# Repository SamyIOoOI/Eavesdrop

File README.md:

<h1 align="center">Eavesdrop</h1>

### <p align="center">[Main Features](#main-features) **-** [Usage](#usage-of-eavesdrop) **-** [PCB & Schematic](#design) **-** [Gerber Files](/Eavesdrop/Gerber%20Files/) **-** [Kicad (Schematic & PCB)](/Eavesdrop/Kicad%20Source%20Files/)  **-** [BOM](#bom)  **-** [BOM (File)](/BOM/evasdrop.xlsx) **-** [Credits](#credits)</p>

## How would you feel if your own fridge was spying on you? Maybe even your tv, maybe the fryer, maybe the wall outlet you charge this device with. maybe even your charger. Well that could very well be a carrier bug. Just like Eavesdrop.

*A "current carrier bug" is a spy tool that records the sound inside the area its plugged in and sends it back through the AC power its connected to directly, evading most detection devices available in the market that rely on RF to detect these devices.*

----------------

**<p align="center">No matter where you are. The bug listens as long as there's electricity flowing in the bugged device.<p>**

---------------

## Main Features

- Undetectable (via RF Detectors that are commonly used)
- Secretive (but requires prior access to the room)

- **Can be planted into any device, your lamp, your tv, your pc, ANYTHING can become a bug with one plug.**

## Usage of Eavesdrop

1- Insert it into the outlet or any device that takes in power from the wall and make sure the microphone jack is connected to proper microphone element such as an electret mic.

2- Connect the passive & active AC wires to their respective locations via the male header on the pcb, each header reads if its N (neutral) or L (live). 
Reversal could cause irreversible damage. Use a test screw driver to make sure you're connecting the right ones.

3- connect the receiver , when required to listen to the broadcast, to an outlet that is in the same grid as the target room/building.

4- Make sure that both the receiver and the sender are at the same wavelength via calibration. Refer to the schemati for more details.

5- Use the volume control knob to increase/decrease th sound level.

<br>

<p align="center">Note that usage of Eavesdrop or any other spying device is illegal when taken out of personal hobby boundaries and used beyond one's own property. (If your device bleeds into the grid of neighbouring properties you may still be fined.) <br><br> I hold no responsiblity on the misuse of this project for illegal activities such as but not limited to: Unathorized Surveillance, Stalking, and damage to property.<br><br>My work is done for the sake of open-sourcing, eduction and self-learning. Not to inflict harm.<p>

## Design

Eavesdrop Sender Schematic

Eavesdrop Sender PCB

Eavesdrop Sender PCB (Model)

Eavesdrop Receiver Schematic

Eavesdrop Receiver PCB

Eavesdrop Receiver PCB (Model)

## BOM

| **Part Name**                           | **Quantity** | **Price** | **Link**                                                                                                   |
|-----------------------------------------|--------------|-----------|------------------------------------------------------------------------------------------------------------|
| **2.54mm 1x2 Pin Header**               | 2            | 89.04     | https://www.digikey.com/en/products/detail/samtec-inc/TSW-102-26-S-S/1103922                               |
| **Capacitor 0.1 uF**                    | 3            | 41.93     | https://www.digikey.com/en/products/detail/vishay-beyschlag-draloric-bc-components/K104K10X7RF5UH5/2356754 |
| **Capacitor 10 nF**                     | 1            | 5.18      | https://www.digikey.com/en/products/detail/samsung-electro-mechanics/CL21B103KBANNNC/3886673               |
| **Capacitor 10 uF**                     | 3            | 29.51     | https://www.digikey.com/en/products/detail/kemet/ESK106M050AC3DA/13176616                                  |
| **Capacitor 100 nF**                    | 6            | 83.87     | https://www.digikey.com/en/products/detail/vishay-beyschlag-draloric-bc-components/K104K10X7RF5UH5/2356754 |
| **Capacitor 100 uF**                    | 4            | 115.96    | https://www.digikey.com/en/products/detail/rubycon/35TZV100M6-3X8/3134900                                  |
| **Capacitor 160 pF**                    | 1            | 1.09      | https://www.digi-electronics.com/en/products/detail/murata-electronics/GCM1885C2A161JA16D/7169978.html     |
| **Capacitor 220 uF**                    | 1            | 31.76     | https://www.lcsc.com/product-detail/C133440.html                                                           |
| **Capacitor 47 uF**                     | 3            | 65.23     | https://www.digikey.com/en/products/detail/rubycon/63ZLJ47M6-3X11/3134467                                  |
| **Capacitor 470pF**                     | 2            | 1.00      | https://uge-one.com/product/ceramic-capacitor-470pf/                                                       |
| **Condenser Microphone**                | 1            | 6.00      | https://makerselectronics.com/product/condenser-microphone-2-pins/                                         |
| **Crystal/Oscillator CFPS-72**          | 1            | 168.77    | https://www.digikey.com/en/products/detail/ecs-inc/ECS-100AX-035/827253                                    |
| **Diode 1N4148**                        | 1            | 5.18      | https://www.digikey.com/en/products/detail/onsemi/1N4148/458603                                            |
| **IC ICL7660**                          | 1            | 51.30     | https://uge-one.com/product/icl7660/                                                                       |
| **IC LM386**                            | 1            | 55.91     | https://www.digikey.com/en/products/detail/texas-instruments/LM386N-1-NOPB/6284                            |
| **IC TL072**                            | 1            | 24.48     | https://www.lcsc.com/product-detail/C7236.html                                                             |
| **Inductor 10µH**                       | 2            | 11.39     | https://www.digikey.com/en/products/detail/tdk/MLZ2012M100WTD25/4743190                                    |
| **Potentiometer 10K**                   | 1            | 96.29     | https://www.digikey.com/en/products/detail/tt-electronics-bi/P160KN-0QD15B10K/2408885                      |
| **Power Supply HLK-PM01 (AC-DC 5V 3W)** | 2            | 320.00    | https://makerselectronics.com/product/hlk-pm01-ac-dc-power-module/                                         |
| **Resistor 10**                         | 1            | 0.15      | https://makerselectronics.com/product/carbon-resistor-10%cf%89-0-25w-through-hole/                         |
| **Resistor 100**                        | 2            | 2.50      | https://uge-one.com/product/resistor-1w-carbon-film-5-tolerance-100r-ohm/                                  |
| **Resistor 100K**                       | 2            | 0.30      | https://makerselectronics.com/product/carbon-resistor-100k-0-25w/                                          |
| **Resistor 10K**                        | 1            | 0.10      | https://makerselectronics.com/product/carbon-resistor-10k%cf%89-0-125w-through/                            |
| **Resistor 2.2K**                       | 1            | 0.10      | https://makerselectronics.com/product/carbon-resistor-2-2k%cf%89-0-125w-through-hole/                      |
| **Resistor 220K**                       | 1            | 0.15      | https://makerselectronics.com/product/carbon-resistor-220k%cf%89-0-25w-through-hole/                       |
| **Resistor 4.7K**                       | 2            | 0.50      | https://uge-one.com/product/carbon-resistor-0-25w-4-7k-ohm/                                                |
| **Resistor 47**                         | 1            | 1.00      | https://makerselectronics.com/product/carbon-resistor-47%cf%89-2w-through-hole/                            |
| **Resistor 47K**                        | 1            | 0.15      | https://makerselectronics.com/product/carbon-resistor-47k%cf%89-0-25w/                                     |
| **Resistor VOLTAGEDIVIDER**             | 1            | 0.15      | https://makerselectronics.com/product/carbon-resistor-100k-0-25w/                                          |
| **Speaker**                             | 1            | 60.00     | https://makerselectronics.com/product/speaker-8-ohm-10w-125x60mm/                                          |
| **Transformer ED8_4**                   | 2            | 755.84    | https://www.digikey.com/en/products/detail/pulse-electronics/HX0068ANL/3025742                             |
| **Transistor BD139**                    | 1            | 4.50      | https://makerselectronics.com/product/bd139-1-5a-80v-npn-bipolar-power-transistor-to-126/                  |
| **Total**                               |              | 2029.33 EGP  |                                                                                                            |

*Credits: BOM converted from XLSX to md on tableconvert.com*

## Credits

Made by SamyIOoOI on github under the GPL 3.0 Licence.

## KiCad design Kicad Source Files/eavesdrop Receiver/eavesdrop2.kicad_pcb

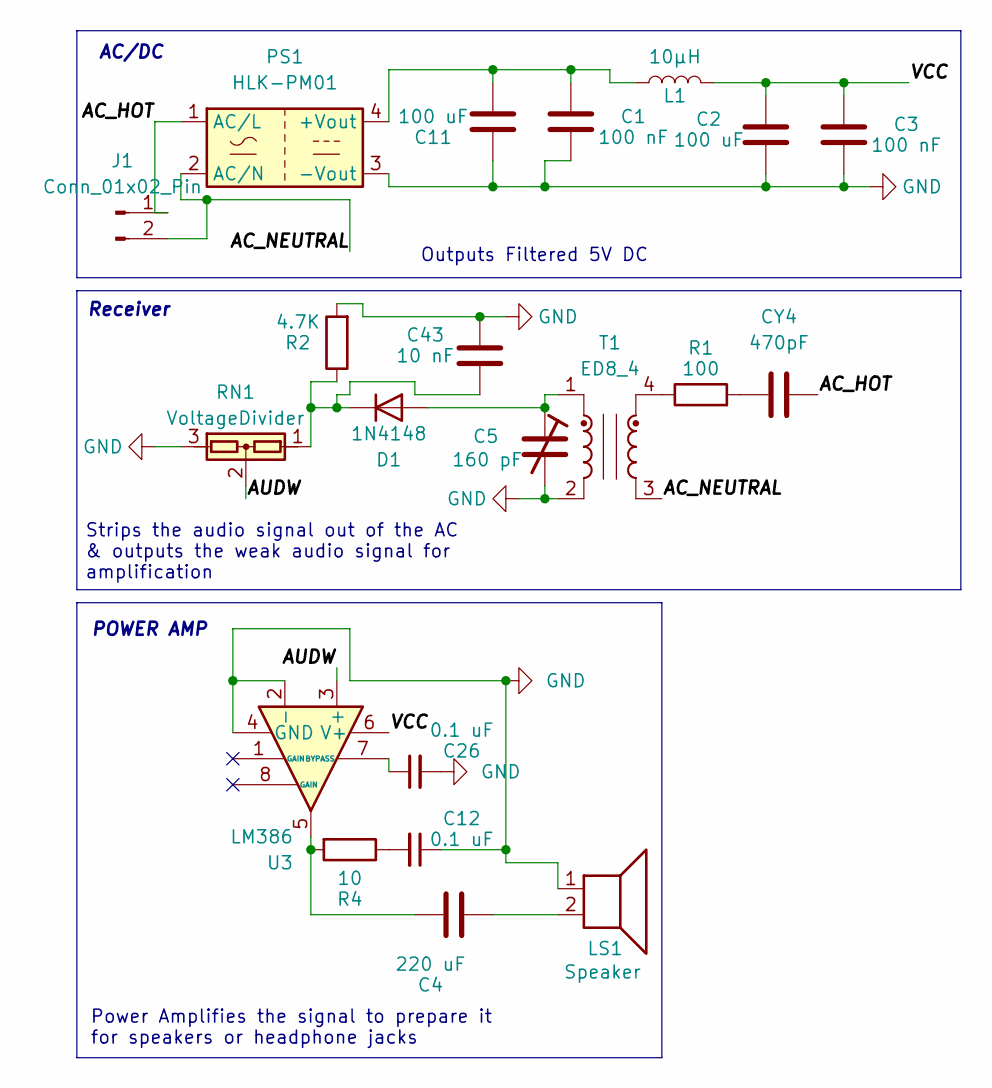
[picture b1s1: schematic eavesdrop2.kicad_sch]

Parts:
C1, C3: 100 nF; C_0603_1608Metric
C2, C11: 100 uF; C_1210_3225Metric
C4: 220 uF; C_1210_3225Metric
C5: 160 pF; C_0603_1608Metric
C12, C26: 0.1 uF; C_0603_1608Metric
C43: 10 nF; C_0603_1608Metric
CY4: 470pF; C_0603_1608Metric
D1: 1N4148; D_DO-35_SOD27_P7.62mm_Horizontal
J1: Conn_01x02_Pin; PinHeader_1x02_P2.54mm_Vertical
L1: 10µH; L_0805_2012Metric
LS1: Speaker; PinHeader_1x02_P2.54mm_Vertical
PS1: HLK-PM01; Converter_ACDC_Hi-Link_HLK-PMxx
R1: 100; R_0603_1608Metric
R2: 4.7K; R_0603_1608Metric
R4: 10; R_0603_1608Metric
RN1: VoltageDivider; SOT-23
T1: ED8_4; Transformer_ED8_4-Lead_10.5x8mm_P5mm
U3: LM386; SOIC-8_3.9x4.9mm_P1.27mm

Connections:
/AC_HOT: CY4.2, J1.1, PS1.1 (AC/L)
/AC_NEUTRAL: J1.2, PS1.2 (AC/N), T1.3
/AUDW: RN1.2, U3.3 (+)
/VCC: C2.2, C3.2, L1.2, U3.6 (V+)
GND: C1.1, C2.1, C3.1, C5.2, C11.1, C12.1, C26.2, C43.1, LS1.1, PS1.3 (-Vout), R2.2, RN1.3, T1.2, U3.2 (-), U3.4 (GND)
unnamed: C4.1, R4.2, U3.5
unnamed: C4.2, LS1.2
unnamed: C12.2, R4.1
unnamed: CY4.1, R1.2
unnamed: C5.1, D1.2 (A), T1.1
unnamed: C43.2, D1.1 (K), R2.1, RN1.1
unnamed: C1.2, C11.2, L1.1, PS1.4 (+Vout)
unnamed: R1.1, T1.4
unnamed: C26.1, U3.7 (BYPASS)

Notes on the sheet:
Strips the audio signal out of the AC & outputs the weak audio signal for amplification
Power Amplifies the signal to prepare it for speakers or headphone jacks
AC/DC
Receiver
POWER AMP
Outputs Filtered 5V DC

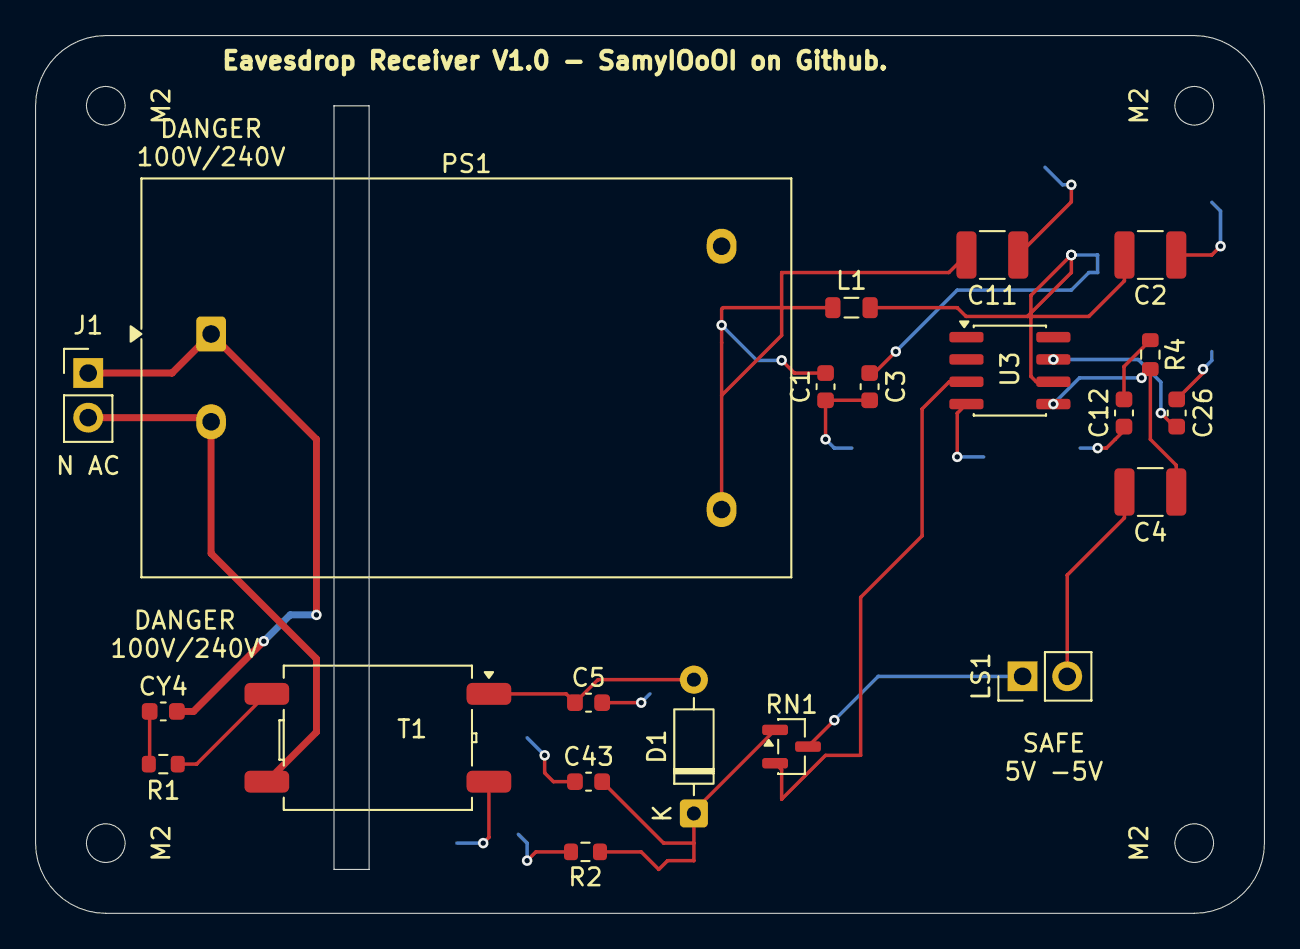
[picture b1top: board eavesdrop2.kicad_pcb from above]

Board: 2 copper layers, 70.0 x 50.0 mm, 25 parts (0 on the bottom side), 14 nets.

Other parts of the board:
M2, M2#2, M2#3, M2#4: MountingHole_2.2mm_M2

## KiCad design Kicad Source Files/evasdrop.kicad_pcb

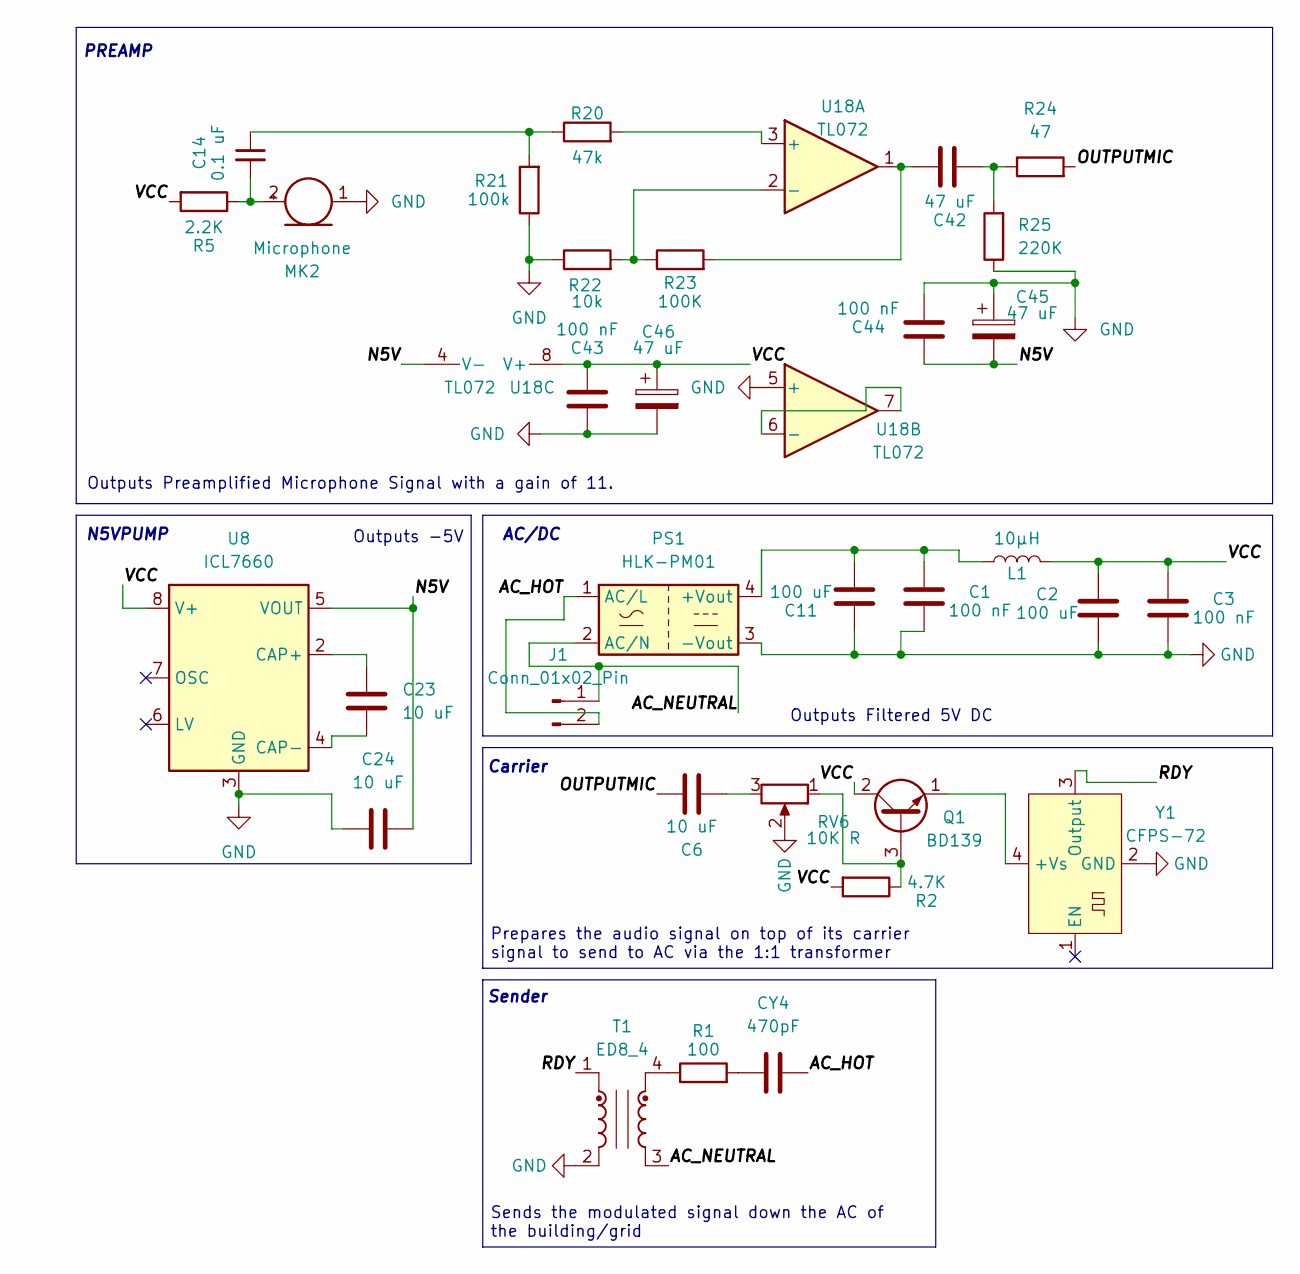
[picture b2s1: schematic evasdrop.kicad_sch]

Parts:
C1, C3, C43, C44: 100 nF; C_0402_1005Metric
C2: 100 uF; C_0402_1005Metric
C6, C23, C24: 10 uF; C_0603_1608Metric
C11: 100 uF; C_1210_3225Metric
C14: 0.1 uF; C_0603_1608Metric
C42, C45, C46: 47 uF; CP_EIA-3216-18_Kemet-A
CY4: 470pF; C_0603_1608Metric
J1: Conn_01x02_Pin; PinHeader_1x02_P2.54mm_Vertical
L1: 10µH; L_0805_2012Metric
MK2: Microphone; PinHeader_1x02_P2.54mm_Vertical
PS1: HLK-PM01; Converter_ACDC_Hi-Link_HLK-PMxx
Q1: BD139; TO-126-3_Vertical
R1: 100; R_0603_1608Metric
R2: 4.7K; R_0603_1608Metric
R5: 2.2K; R_0603_1608Metric
R20: 47k; R_0603_1608Metric
R21: 100k; R_0603_1608Metric
R22: 10k; R_0603_1608Metric
R23: 100K; R_0603_1608Metric
R24: 47; R_0603_1608Metric
R25: 220K; R_0603_1608Metric
RV6: 10K R; Potentiometer_Bourns_TC33X_Vertical
T1: ED8_4; Transformer_ED8_4-Lead_10.5x8mm_P5mm
U8: ICL7660; SOIC-8_3.9x4.9mm_P1.27mm
U18: TL072; SOIC-8_3.9x4.9mm_P1.27mm
Y1: CFPS-72; Oscillator_SMD_IQD_IQXO70-4Pin_7.5x5.0mm

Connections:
/AC_HOT: CY4.2, J1.2, PS1.1 (AC/L); also elsewhere on the board
/AC_NEUTRAL: J1.1, PS1.2 (AC/N), T1.3; also elsewhere on the board
/N5V: C24.1, C44.2, C45.2, U8.5 (VOUT), U18.4 (V-)
/OUTPUTMIC: C6.1, R24.2
/RDY: T1.1, Y1.3 (Output)
/VCC: C2.2, C3.2, C43.1, C46.1, L1.2, Q1.2 (C), R2.2, R5.2, U8.8 (V+), U18.8 (V+)
GND: C1.1, C2.1, C3.1, C11.1, C24.2, C43.2, C44.1, C45.1, C46.2, MK2.1 (-), PS1.3 (-Vout), R21.1, R22.1, R25.1, RV6.2, T1.2, U8.3 (GND), U18.5 (+), Y1.2 (GND)
unnamed: C6.2, RV6.3
unnamed: C14.1, R20.1, R21.2
unnamed: C42.1, R23.2, U18.1
unnamed: C42.2, R24.1, R25.2
unnamed: CY4.1, R1.2
unnamed: C14.2, MK2.2 (+), R5.1
unnamed: C1.2, C11.2, L1.1, PS1.4 (+Vout)
unnamed: Q1.3 (B), R2.1, RV6.1
unnamed: Q1.1 (E), Y1.4 (+Vs)
unnamed: R1.1, T1.4
unnamed: C23.1, U8.2 (CAP+)
unnamed: C23.2, U8.4 (CAP-)
unnamed: R20.2, U18.3 (+)
unnamed: R22.2, R23.1, U18.2 (-)
unnamed: U18.6 (-), U18.7

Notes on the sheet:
Sender
Outputs Preamplified Microphone Signal with a gain of 11.
PREAMP
Carrier
AC/DC
Prepares the audio signal on top of its carrier signal to send to AC via the 1:1 transformer
N5VPUMP
Sends the modulated signal down the AC of the building/grid
Outputs -5V
Outputs Filtered 5V DC

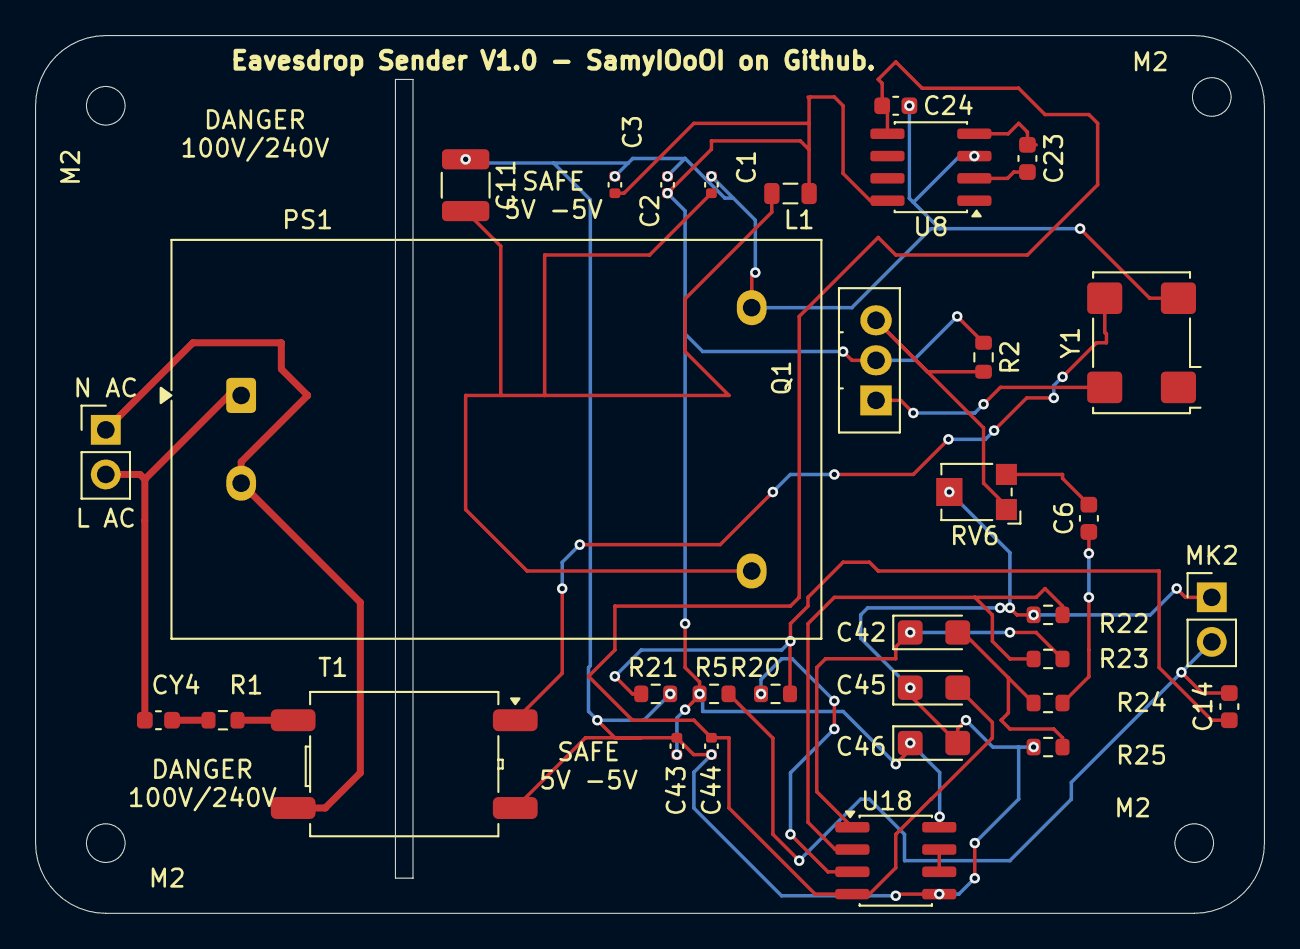
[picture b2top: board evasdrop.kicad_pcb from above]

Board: 2 copper layers, 70.0 x 50.0 mm, 37 parts (0 on the bottom side), 22 nets.

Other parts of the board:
M2, M2#2, M2#3, M2#4: MountingHole_2.2mm_M2
N AC: Conn_01x02_Pin; PinHeader_1x02_P2.54mm_Vertical

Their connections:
/AC_HOT: N AC.2; also elsewhere on the board
/AC_NEUTRAL: N AC.1; also elsewhere on the board
